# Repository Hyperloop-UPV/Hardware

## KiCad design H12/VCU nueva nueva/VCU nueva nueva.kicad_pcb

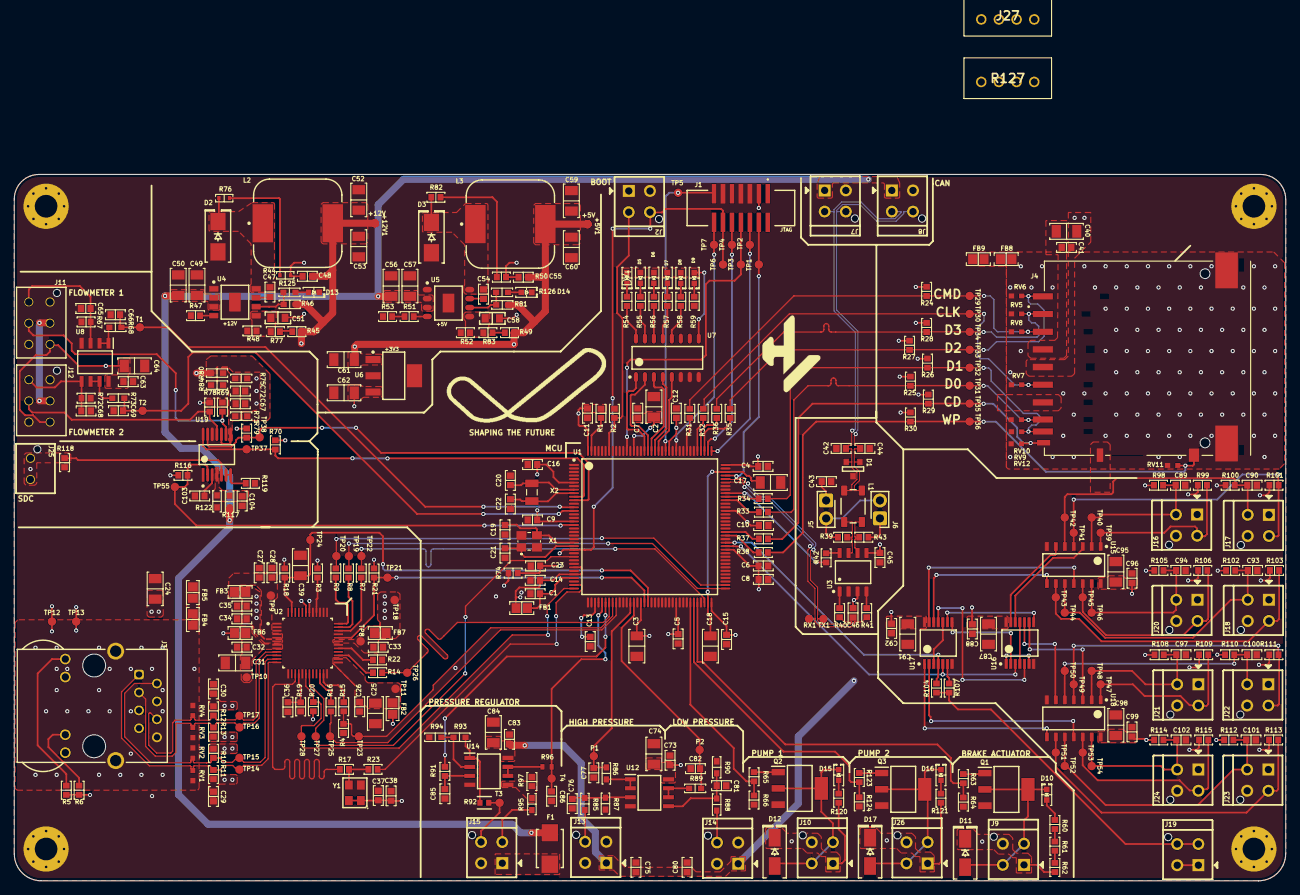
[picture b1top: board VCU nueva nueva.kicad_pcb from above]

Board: 6 copper layers, 180.0 x 100.0 mm, 388 parts (0 on the bottom side), 207 nets.

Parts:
+5V, +5V1, +12V, +12V1: Test point 1.2mm; Test point 1.2mm-Footprint-1
C1, C4, C5, C6, C7, C8, C9, C10, C11, C12, C13, C14, C15, C23, C26, C27, C28, C29, C30, C32, C33, C34, C37, C41, C45, C46, C47, C54, C63, C66, C67, C69, C72, C73, C75, C77, C80, C82, C83, C85, C86, C88, C89, C90, C92, C93, C94, C96, C97, C99, C100, C101, C102, C103, C104: 0.1 µF; CAP 0603_1608
C2, C24, C39, C40, C61, C62: 10 µF; CAP 1206_3216 - 0.8MM
C3: 4.7 µF; CAP 1206_3216 - 0.8MM
C16: 4700 pF; CAP 0603_1608
C17, C18: 2.2 µF; CAP 1206_3216 - 0.8MM
C19, C21: 12pF; CAP 0603_1608
C20, C22: 6.8 pF; CAP 0603_1608
C25, C31: 22 µF; CAP 1206_3216 - 0.8MM
C35, C38: 1 µF; CAP 0603_1608
C36: 100 pF; CAP 0603_1608
C42, C44: 47 pF; CAP 0603_1608
C43: 4700pF; CAP 0603_1608
C48: 1200 pF; CAP 0603_1608
C49, C50, C56, C57: 2.2µF; CAP 1206_3216 - 1.8MM
C51: 47 pF; MURATA GQM187 0603_1608
C52, C53, C59, C60: 22µF; CAP 1206_3216 - 1.8MM
C55: 2200pF; CAP 0603_1608
C58: 56 pF; MURATA GQM187 0603_1608
C64, C74, C84, C87, C91, C95, C98: 1 µF; CAP 1206_3216 - 0.8MM
C65, C68: 3300pF; CAP 0603_1608
C76, C81: 1500 pF; CAP 0603_1608
D1: PESD1CAN,215; PESD1CAN,215-Footprint-1
D2, D3: SK510BH-LTP; DO214AA SMB
D4, D9, D10, D13, D14, D15, D16: Green; LED 0603_1608 GREEN
D5: Red; LED 0603_1608 RED
D6: Blue; LED 0603_1608 BLUE
D7: Yellow; LED 0603_1608 YELLOW
D8: White; LED 0603_1608
D11, D12, D17: RS1B-13-F; DO214AC SMA
F1: 0308.500UR; New footprint 1
FB1, FB2, FB3, FB4, FB5, FB6, FB7, FB8, FB9: 120 Ohms @ 100 MHz; FER 0805_2012
J1: 3221-14-0300-00
J2, J7, J8, J9, J10, J13, J14, J15, J16, J17, J18, J19, J20, J21, J22, J23, J24, J26: 206832-0401; 206832-0401-Footprint-1
J3: 7499011222A
J4: 1939115-1; TE_1939115-1
J5, J6: 22-28-4020; 22-28-4020-Footprint-1
J11, J12: 206832-0602
J25: 216571-2002; 216571-2002-Footprint-1
J27: B4B-XH-A_LF__SN_; B4BXHALFSN
L1: DLW43SH510XK2L; FP-DLW43-0_2-t2_6-e0_7-MFG
L2: 7447709220; WE-PD_1210
L3: 744771112; WE-PD_1260
P1, P2: Test point 1.2mm; Test point 1.2mm-Footprint-1
Q1, Q2, Q3: BUK9875-100A/CUX; BUK9875-100A_CUX-Footprint-1
R1, R2, R3, R4, R18, R20, R21, R22, R24, R25, R26, R27, R28, R29, R30, R67, R69, R70, R72, R74, R78, R79, R116, R118, R119: 10 kOhms; RES 0603_1608
R5, R6, R63, R65, R123: 330 Ohms; RES 0603_1608
R7, R8, R9, R14, R15, R16, R17, R23, R31, R32, R33, R34, R35, R36, R37, R38: 33 Ohms; RES 0603_1608
R10, R11, R12, R13: 49.9 Ohms; RES 0603_1608
R19: 6.49 kOhms; RES 0603_1608
R39, R43: 62 Ohms; RES 0603_1608
R40, R41, R42: 100 Ohms; RES 0603_1608
R44: 330 kOhms; KOA RES RK73 RN73 0603_1608
R45: 220 kOhms; RES 0603_1608
R46: 10 kOhms; YAGEO RES 0603_1608
R47, R48, R52, R91: 100 kOhms; RES 0603_1608
R49: 56 kOhms; RES 0603_1608
R50, R97: 68 kOhms; RES 0603_1608
R51, R98, R99, R100, R101, R102, R103, R105, R106, R108, R109, R110, R111, R112, R113, R114, R115: 39 kOhms; RES 0603_1608
R53: 2.2 kOhms; RES 0603_1608
R54, R55, R56, R57, R58, R59, R60, R61, R62: 1 kOhms; RES 0603_1608
R64, R66, R124: 10kOhms; RES 0603_1608
R68, R73, R86, R89: 1 kOhms; YAGEO RES 0603_1608
R71, R80: 47kOhms; YAGEO RES 0603_1608
R75, R84, R94: 10kOhms; YAGEO RES 0603_1608
R76: 2.2 kOhms; KOA RES RK73 RN73 0603_1608
R77: 680 kOhms; RES 0603_1608
R81: 2.7 kOhms; YAGEO RES 0603_1608
R82: 180 kOhms; RES 0603_1608
R83: 270 kOhms; RES 0603_1608
R85, R88: 12kOhms; YAGEO RES 0603_1608
R87, R90: 33kOhms; YAGEO RES 0603_1608
R92: 0 Ohm; FP-CRG0603-IPC_C
R93: 5.1kOhms; YAGEO RES 0603_1608
R95: 39 kOhms; YAGEO RES 0603_1608
R96: 1kOhms; RESC1608X55X25LL10T15
R104, R107: 0 Ohms; RES 0603_1608
R117: 100 kOhms; YAGEO RES 0603_1608
R120, R121: 1.5 kOhms; RES 0603_1608
R122: 270 kOhms; YAGEO RES 0603_1608
R125, R126: 10 Ohms; YAGEO RES 0603_1608
R127: 4.7k; B4BXHALFSN
RV1, RV2, RV3, RV4, RV5, RV6, RV7, RV8, RV9, RV10, RV11, RV12: 82306050029; WE-VE ULC_0603
RX1: Test point 1.2mm; Test point 1.2mm-Footprint-1
SC1, SC2, SC3, SC4: M3 Screw; M3 Screw-Footprint-1
T1, T2, T3, T4: Test point 1.2mm; Test point 1.2mm-Footprint-1
TP1, TP2, TP3, TP4, TP5, TP6, TP7, TP8, TP9, TP10, TP11, TP12, TP13, TP14, TP15, TP16, TP17, TP18, TP19, TP20, TP21, TP22, TP23, TP24, TP25, TP26, TP27, TP28, TP29, TP30, TP31, TP32, TP33, TP34, TP35, TP36, TP37, TP38, TP39, TP40, TP41, TP42, TP43, TP44, TP45, TP46, TP47, TP48, TP49, TP50, TP51, TP52, TP53, TP54, TP55: Test point 1.2mm; Test point 1.2mm-Footprint-1
TX1: Test point 1.2mm; Test point 1.2mm-Footprint-1
U1: STM32H723ZG; TSQFP50P2200X2200X160-144N
U2: KSZ8041TLI; FP-TQFP7X7-48LD-PL-1-MFG
U3: TJA1051T/3,118; NXP-SOIC-8_N
U4, U5: LM5013-Q1; SOIC127P600X170_HS-9N
U6: LT1963AEST-3.3#TRPBF; SOT230P700X180-4N
U7: ULN2002A; SOIC16
U8, U12, U14: MCP6022-E/SN; SOIC-SN8_N
U15, U18: SN74HC32DR; D0014A_L
U16, U17: SN74ALVC08IPWRQ1; PW0014A_N
U19: LM339PWR; FP-PW0014A-IPC_A
X1: 25.000MHZ; ABM8G-25.000MHZ-18-D2Y-T-Footprint-1
X2: 32.768KHZ; ABS07-120-32.768KHZ-T-Footprint-1
Y1: 50 MHz; ABRACON ASE

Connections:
+3V3: C2.2, C3.2, C4.2, C5.2, C6.2, C7.2, C8.2, C9.2, C10.2, C11.2, C12.2, C13.2, C14.2, C15.2, C16.2, C24.2, C37.2, C38.2, C40.2, C41.2, C45.2, C62.2, C63.2, C64.1, C73.2, C74.1, C87.2, C88.2, C91.2, C92.2, C95.2, C96.2, C98.2, C99.2, D4.1, D5.1, D6.1, D7.1, D8.1, D9.1, FB1.2, FB2.2, FB6.2, J1.3 (VCC), J3.4 (CTD), J3.5 (CRD), J4.4, J11.4, J12.4, R1.2, R3.2, R5.2, R6.2, R18.2, R20.2, R21.2, R24.2, R25.2, R26.2, R27.2, R28.2, R29.2, R30.2, R69.2, R70.2, R74.1, R78.2, R79.2, R98.2, R99.2, R100.2, R101.2, R102.2, R103.2, R105.2, R106.2, R108.2, R109.2, R110.2, R111.2, R112.2, R113.2, R114.2, R115.2, R116.2, U1.6 (VBAT), U1.17 (VDD), U1.30 (VDD), U1.32 (VREF+), U1.39 (VDD), U1.52 (VDD), U1.62 (VDD), U1.72 (VDD), U1.84 (VDD), U1.95 (VDD33USB), U1.108 (VDD), U1.121 (VDD), U1.131 (VDD), U1.144 (VDD), U3.5 (VIO), U6.3 (OUT), U7.9, U8.8 (VDD), U12.8 (VDD), U15.14 (VCC), U16.14 (VCC), U17.14 (VCC), U18.14 (VCC), Y1.1 (TRI), Y1.4 (VDD)
+5V: +5V.1, +5V1.1 (*_1), C46.2, C55.2, C59.2, C60.2, C61.2, C75.2, C80.2, C83.2, C84.1, J13.1, J14.1, L3.2, R49.2, R81.2, U3.3 (VCC), U6.1 (IN), U14.8 (VDD)
+12V: +12V.1, +12V1.1 (*_1), C48.2, C52.2, C53.2, D12.2, D17.2, J10.1, J10.4, J11.5, J12.5, J26.1, J26.4, L2.2, R45.2, R46.2, R71.2, R80.2, R120.2, R121.2
+24: C103.2, U19.3 (VCC)
+24_SDC: D11.2, J9.1, J9.4, J25.1, J25.2, R62.2, R118.2, U19.5 (2IN+)
/Bomba_Refri/BOMBA_1: R65.1, R66.2
/Bomba_Refri/BOMBA_2: R123.1, R124.2
/Bomba_Refri/Bomba_TACH: J27.2, R127.2
/Braking_Sensor/GD_Reset_bypass: J19.3, J19.4, R104.2, R107.2
/Braking_Sensor/RESET: R104.1, U1.86 (PD15), U17.4 (2A)
/Braking_Sensor/SENSOR_1: J16.2, R99.1, TP39.1 (*_1), U15.1 (1A)
/Braking_Sensor/SENSOR_2: C89.2, J16.3, R98.1, TP40.1 (*_1), U15.2 (1B)
/Braking_Sensor/SENSOR_3: J17.2, R101.1, TP41.1 (*_1), U15.4 (2A)
/Braking_Sensor/SENSOR_4: C90.2, J17.3, R100.1, TP42.1 (*_1), U15.5 (2B)
/Braking_Sensor/SENSOR_5: J18.2, R103.1, TP43.1 (*_1), U15.9 (3A)
/Braking_Sensor/SENSOR_6: C93.2, J18.3, R102.1, TP44.1 (*_1), U15.10 (3B)
/Braking_Sensor/SENSOR_7: J20.2, R106.1, TP45.1 (*_1), U15.12 (4A)
/Braking_Sensor/SENSOR_8: C94.2, J20.3, R105.1, TP46.1 (*_1), U15.13 (4B)
/Braking_Sensor/SENSOR_9: J21.2, R109.1, TP47.1 (*_1), U18.1 (1A)
/Braking_Sensor/SENSOR_10: C97.2, J21.3, R108.1, TP48.1 (*_1), U18.2 (1B)
/Braking_Sensor/SENSOR_11: J22.2, R111.1, TP49.1 (*_1), U18.4 (2A)
/Braking_Sensor/SENSOR_12: C100.2, J22.3, R110.1, TP50.1 (*_1), U18.5 (2B)
/Braking_Sensor/SENSOR_13: J23.2, R113.1, TP51.1 (*_1), U18.9 (3A)
/Braking_Sensor/SENSOR_14: C101.2, J23.3, R112.1, TP52.1 (*_1), U18.10 (3B)
/Braking_Sensor/SENSOR_15: J24.2, R115.1, TP53.1 (*_1), U18.12 (4A)
/Braking_Sensor/SENSOR_16: C102.2, J24.3, R114.1, TP54.1 (*_1), U18.13 (4B)
/CAN/CAN1_N: R41.1, RX1.1 (*_1)
/CAN/CAN1_P: R40.1, TX1.1 (*_1)
/CAN/CANT_N: L1.4, R43.2, U3.6 (CANL)
/CAN/CANT_P: L1.1, R39.1, U3.7 (CANH)
/CAN/CAN_N: C44.1, D1.1, J7.4, J8.4, L1.3
/CAN/CAN_P: C42.2, D1.2, J7.3, J8.3, L1.2
/Caudalimetro/2.1V_Reference: C67.2, C72.2, R71.1, R75.2, R80.1, R84.2, U19.8 (3IN-), U19.10 (4IN-)
/Caudalimetro/FLOW_1: R70.1, TP37.1 (*_1), U1.10 (PF0), U19.14 (OUT3)
/Caudalimetro/FLOW_2: R79.1, TP38.1 (*_1), U1.11 (PF1), U19.13 (OUT4)
/Caudalimetro/FLOW_SENS_1: J11.2, R69.1, U19.9 (3IN+)
/Caudalimetro/FLOW_SENS_2: J12.2, R78.1, U19.11 (4IN+)
/Caudalimetro/NTC_TEMP_1: C66.2, R68.2, T1.1 (*_1), U1.13 (PF3)
/Caudalimetro/NTC_TEMP_2: C69.2, R73.2, T2.1 (*_1), U1.14 (PF4)
/Caudalimetro/TEMP_SENS_1: C65.1, J11.3, R67.1, U8.3 (VINA+)
/Caudalimetro/TEMP_SENS_2: C68.1, J12.3, R72.1, U8.5 (VINB+)
/Electrovalvula/ELECTROVALVULA: R63.1, R64.2, U1.68 (PE15)
/Ethernet_PHY/CONFIG0: R3.1, U2.40 (COL/CONFIG0)
/Ethernet_PHY/CRS: R14.2, TP26.1 (*_1), U1.43 (PA7)
/Ethernet_PHY/CRS_HF: R14.1, U2.27 (RXDV/CRSDV/CONFIG2)
/Ethernet_PHY/LAN_INTE: R21.1, TP21.1 (*_1), U1.53 (PF13), U2.32 (INTRP)
/Ethernet_PHY/LED0: J3.10, TP12.1 (*_1), U2.42 (LED0/NWAYEN)
/Ethernet_PHY/LED1: J3.12, TP13.1 (*_1), U2.43 (LED1/SPEED)
/Ethernet_PHY/MDC: TP27.1 (*_1), U1.27 (PC1), U2.19 (MDC)
/Ethernet_PHY/MDIO: R20.1, TP28.1 (*_1), U1.36 (PA2), U2.18 (MDIO)
/Ethernet_PHY/PHY_CLK_50M: R17.2, U2.15 (XI/REFCLK/CLOCK)
/Ethernet_PHY/PHY_RST: C39.2, R18.1, TP24.1 (*_1), U1.54 (PF14), U2.47 (~RST)
/Ethernet_PHY/REXT: C36.2, R19.2, U2.16 (REXT)
/Ethernet_PHY/RXD0: R4.2, R15.2, TP23.1 (*_1), U1.44 (PC4)
/Ethernet_PHY/RXD0_HF: R15.1, U2.23 (RXD0/RXD[0]/RX_DUPLEX)
/Ethernet_PHY/RXD1: R16.2, TP25.1 (*_1), U1.45 (PC5)
/Ethernet_PHY/RXD1_HF: R16.1, U2.22 (RXD1/RXD[1]/PHYAD2)
/Ethernet_PHY/RXER: R22.2, U2.29 (RXER/RX_ER/ISO)
/Ethernet_PHY/RX_N: J3.6 (RD-), R12.2, RV4.1, TP17.1 (*_1), U2.9 (RX-)
/Ethernet_PHY/RX_P: J3.3 (RD+), R13.2, RV3.1, TP16.1 (*_1), U2.10 (RX+)
/Ethernet_PHY/TXD0: R8.1, TP19.1 (*_1), U1.73 (PB12)
/Ethernet_PHY/TXD0_HF: R8.2, U2.35 (TXD0/TXD[0]/TX)
/Ethernet_PHY/TXD1: R9.1, TP20.1 (*_1), U1.74 (PB13)
/Ethernet_PHY/TXD1_HF: R9.2, U2.36 (TXD1/TXD[1]/SYNC)
/Ethernet_PHY/TXEN: R7.1, TP22.1 (*_1), U1.70 (PB11)
/Ethernet_PHY/TXEN_HF: R7.2, U2.34 (TXEN/TX_EN)
/Ethernet_PHY/TX_N: J3.2 (TD-), R10.2, RV2.1, TP15.1 (*_1), U2.11 (TX-)
/Ethernet_PHY/TX_P: J3.1 (TD+), R11.2, RV1.1, TP14.1 (*_1), U2.12 (TX+)
/Info_LEDs/LED_CAN: U1.125 (PG10), U7.4
/Info_LEDs/LED_CONNECTING: U1.126 (PG11), U7.3
/Info_LEDs/LED_FAULT: U1.127 (PG12), U7.2
/Info_LEDs/LED_OPERATIONAL: U1.128 (PG13), U7.1
/Info_LEDs/LED_SLEEP: U1.124 (PG9), U7.5
/MCU/BOOT: J2.3, R2.1, U1.138 (BOOT0)
/MCU/FAULT_BRAKE: U1.85 (PD14), U16.3 (1Y), U17.5 (2B)
/MCU/HIGH_PRESSURE: C77.2, P1.1 (*_1), R86.2, U1.49 (PF11)
/MCU/HSE_IN: C19.2, U1.23 (PH0-OSC_IN), X1.3 (XTAL2)
/MCU/HSE_OUT: C21.2, U1.24 (PH1-OSC_OUT), X1.1 (XTAL1)
/MCU/JTCK-SWCLK: J1.6 (JCLK/SWCLK), TP2.1 (*_1), U1.109 (PA14(SWCLK))
/MCU/JTDI: J1.10 (JTDI), TP4.1 (*_1), U1.110 (PA15(JTDI))
/MCU/JTDO-SWO: J1.8 (JTDO/SWO), TP3.1 (*_1), U1.133 (PB3(JTDO/TSWO))
/MCU/JTMS-SWDIO: J1.4 (JTMS/SWDIO), TP1.1 (*_1), U1.105 (PA13(SWDIO))
/MCU/LOW_PRESSURE: C82.2, P2.1 (*_1), R89.2, U1.50 (PF12)
/MCU/LSE_IN: C20.2, U1.8 (PC14-OSC32_IN), X2.2 (XTAL2)
/MCU/LSE_OUT: C22.2, U1.9 (PC15-OSC32_OUT), X2.1 (XTAL1)
/MCU/NRST: C23.2, J1.12 (NRST), J2.4, R74.2, TP6.1 (*_1), U1.25 (~nRST)
/MCU/REGULADOR_IN: R91.1, U1.42 (PA6)
/MCU/REGULADOR_OUT: C86.2, R96.2, T4.1 (*_1), U1.41 (PA5)
/MCU/SDC: R116.1, TP55.1 (*_1), U1.18 (PF6), U19.2 (2OUT)
/MCU/SDMMC_CD: R37.1, U1.89 (PG4)
/MCU/SDMMC_CLK: R32.1, U1.113 (PC12)
/MCU/SDMMC_CMD: R31.1, U1.116 (PD2)
/MCU/SDMMC_D0: R33.1, U1.98 (PC8)
/MCU/SDMMC_D1: R34.1, U1.99 (PC9)
/MCU/SDMMC_D2: R35.1, U1.111 (PC10)
/MCU/SDMMC_D3: R36.1, U1.112 (PC11)
/MCU/SDMMC_WP: R38.1, U1.88 (PG3)
/MCU/SLNT_MCU: R42.2, U1.100 (PA8)
/MCU/UART_RX: J1.13 (UART_RX), TP5.1 (*_1), U1.122 (PD6)
/MCU/UART_TX: J1.14 (UART_TX), TP7.1 (*_1), U1.119 (PD5)
/Power Supply/FB_5V: C58.1, R52.2, R83.1, U5.5 (FB)
/Power Supply/FB_12V: C51.1, R48.2, R77.1, U4.5 (FB)
/Power Supply/PGOOD_5V: R81.1, R126.2, U5.6 (PGOOD)
/Power Supply/PGOOD_12V: R46.1, R125.2, U4.6 (PGOOD)
/Regulador_Presion/3.18V: R95.1, R97.2, U14.5 (VINB+)
/Regulador_Presion/REG_IN: J15.4, R92.2, T3.1 (*_1)
/Regulador_Presion/REG_OUT: J15.3, R95.2
/Regulador_Presion/V_SUPPLY_1: F1.2, J15.1
/SD/SDMMC_CD_HF: J4.10 (CD), R29.1, R37.2, RV12.1, TP35.1 (*_1)
/SD/SDMMC_CLK_HF: J4.5, R32.2, RV7.1, TP30.1 (*_1)
/SD/SDMMC_CMD_HF: J4.2, R24.1, R31.2, RV8.1, TP29.1 (*_1)
/SD/SDMMC_D0_HF: J4.7, R25.1, R33.2, RV10.1, TP31.1 (*_1)
/SD/SDMMC_D1_HF: J4.8, R26.1, R34.2, RV9.1, TP32.1 (*_1)
/SD/SDMMC_D2_HF: J4.9, R27.1, R35.2, RV6.1, TP33.1 (*_1)
/SD/SDMMC_D3_HF: J4.1, R28.1, R36.2, RV5.1, TP34.1 (*_1)
/SD/SDMMC_WP_HF: J4.12 (WP), R30.1, R38.2, RV11.1, TP36.1 (*_1)
/SDC/18V_Reference: C104.2, R117.1, R122.2, U19.4 (2IN-)
/Transductores_Presion/PRESS_SENS_1: C76.2, R85.1, R87.2, U12.3 (VINA+)
/Transductores_Presion/PRESS_SENS_2: C81.2, R88.1, R90.2, U12.5 (VINB+)
ETH_Shield: FB4.1, J3.Shell (Shield), RV1.2, RV2.2, RV3.2, RV4.2
GND: C1.1, C2.1, C3.1, C4.1, C5.1, C6.1, C7.1, C8.1, C9.1, C10.1, C11.1, C12.1, C13.1, C14.1, C15.1, C16.1, C17.1, C18.1, C19.1, C20.1, C21.1, C22.1, C23.1, C24.1, C25.1, C26.1, C27.1, C28.1, C29.1, C30.1, C31.1, C32.1, C33.1, C34.1, C35.1, C36.1, C37.1, C38.1, C39.1, C40.1, C41.1, C42.1, C43.1, C44.2, C45.1, C46.1, C49.1, C50.1, C52.1, C53.1, C56.1, C57.1, C59.1, C60.1, C61.1, C62.1, C63.1, C64.2, C65.2, C66.1, C67.1, C68.2, C69.1, C72.1, C73.1, C74.2, C75.1, C76.1, C77.1, C80.1, C81.1, C82.1, C83.1, C84.2, C85.1, C86.1, C87.1, C88.1, C89.1, C90.1, C91.1, C92.1, C93.1, C94.1, C95.1, C96.1, C97.1, C98.1, C99.1, C100.1, C101.1, C102.1, C103.1, C104.1, D1.3, D2.1, D3.1, D13.2, D14.2, FB5.2, FB9.2, J1.5 (GND), J1.7 (GND), J1.11 (GND_Det), J2.1, J2.2, J3.8 (GND), J4.3, J4.6, J4.11 (COMM), J7.2, J8.2, J11.1, J11.6, J12.1, J12.6, J13.2, J13.3, J14.2, J14.3, J15.2, J16.1, J16.4, J17.1, J17.4, J18.1, J18.4, J19.1, J19.2, J20.1, J20.4, J21.1, J21.4, J22.1, J22.4, J23.1, J23.4, J24.1, J24.4, Q1.3 (S), Q2.3 (S), Q3.3 (S), R2.2, R4.1, R19.1, R22.1, R47.1, R48.1, R52.1, R53.1, R59.1, R64.1, R66.1, R67.2, R72.2, R75.1, R84.1, R87.1, R90.1, R94.1, R97.1, R118.1, R119.1, R122.1, R124.1, SC1.1 (1_1), SC2.1 (1_1), SC3.1 (1_1), SC4.1 (1_1), U1.1 (PE2), U1.2 (PE3), U1.3 (PE4), U1.4 (PE5), U1.5 (PE6), U1.7 (PC13), U1.12 (PF2), U1.15 (PF5), U1.16 (VSS), U1.19 (PF7), U1.20 (PF8), U1.21 (PF9), U1.22 (PF10), U1.26 (PC0), U1.28 (PC2_C), U1.29 (PC3_C), U1.31 (VSSA), U1.34 (PA0), U1.37 (PA3), U1.38 (VSS), U1.40 (PA4), U1.46 (PB0), U1.47 (PB1), U1.48 (PB2), U1.51 (VSS), U1.55 (PF15), U1.56 (PG0), U1.57 (PG1), U1.58 (PE7), U1.59 (PE8), U1.60 (PE9), U1.61 (VSS), U1.63 (PE10), U1.64 (PE11), U1.65 (PE12), U1.69 (PB10), U1.75 (PB14), U1.76 (PB15), U1.77 (PD8), U1.78 (PD9), U1.79 (PD10), U1.80 (PD11), U1.81 (PD12), U1.82 (PD13), U1.83 (VSS), U1.87 (PG2), U1.90 (PG5), U1.91 (PG6), U1.92 (PG7), U1.93 (PG8), U1.94 (VSS), U1.96 (PC6), U1.97 (PC7), U1.101 (PA9), U1.102 (PA10), U1.107 (VSS), U1.114 (PD0), U1.115 (PD1), U1.117 (PD3), U1.118 (PD4), U1.120 (VSS), U1.123 (PD7), U1.129 (PG14), U1.130 (VSS), U1.132 (PG15), U1.134 (PB4(~nJTRST)), U1.135 (PB5), U1.136 (PB6), U1.137 (PB7), U1.139 (PB8), U1.140 (PB9), U1.141 (PE0), U1.142 (PE1), U2.1 (GND), U2.2 (GND), U2.3 (GND), U2.13 (GND), U2.17 (GND), U2.24 (GND), U2.30 (GND), U2.33 (TXC), U2.37 (GND), U2.38 (TXD2), U2.39 (TXD3), U2.41 (CRS/CONFIG1), U3.2 (GND), U4.1 (GND), U4.9 (PGND), U5.1 (GND), U5.9 (PGND), U6.2 (GND), U6.4 (TAB), U7.6, U7.7, U7.8, U8.4 (VSS), U12.4 (VSS), U14.4 (VSS), U15.7 (GND), U16.7 (GND), U17.7 (GND), U18.7 (GND), U19.12 (GND), X1.2 (GND), X1.4 (GND), Y1.2 (GND)
unnamed: C29.2, R10.1, R11.1
unnamed: C30.2, R12.1, R13.1
unnamed: C43.2, J5.1
unnamed: C48.1, C51.2, R44.2
unnamed: C55.1, C58.2, R50.2
unnamed: D4.2, R54.2
unnamed: D5.2, R55.2
unnamed: D6.2, R56.2
unnamed: D7.2, R57.2
unnamed: D8.2, R58.2
unnamed: D9.2, R59.2
unnamed: D10.1, R60.1
unnamed: D10.2, D11.1, J9.2, J9.3, Q1.2 (D), Q1.4 (D)
unnamed: D12.1, D15.2, J10.2, J10.3, Q2.2 (D), Q2.4 (D)
unnamed: D13.1, R125.1
unnamed: D14.1, R126.1
unnamed: D15.1, R120.1
unnamed: D16.1, R121.1
unnamed: D16.2, D17.1, J26.2, J26.3, Q3.2 (D), Q3.4 (D)
unnamed: FB4.2, FB5.1
unnamed: FB8.2, FB9.1
unnamed: J3.9, R5.1
unnamed: J3.11, R6.1
unnamed: J5.2, J6.2, R39.2
unnamed: J6.1, R43.1
unnamed: J13.4, R85.2
unnamed: J14.4, R88.2
unnamed: Q1.1 (G), R63.2
unnamed: Q2.1 (G), R65.2
unnamed: Q3.1 (G), R123.2
unnamed: R44.1, R76.2
unnamed: R45.1, R77.2
unnamed: R49.1, R83.2
unnamed: R50.1, R82.2
unnamed: R51.2, R53.2
unnamed: R54.1, U7.16
unnamed: R55.1, U7.15
unnamed: R56.1, U7.14
unnamed: R57.1, U7.13
unnamed: R58.1, U7.12
unnamed: R60.2, R61.1
unnamed: R61.2, R62.1
unnamed: R1.1, U1.143 (PDR_ON)
unnamed: R41.2, U3.4 (RXD)
unnamed: R42.1, U3.8 (S)
unnamed: R40.2, U3.1 (TXD)
unnamed: C47.1, U4.7 (BST)
unnamed: R47.2, U4.4 (RON)
unnamed: C47.2, D2.2, L2.1, R76.1, U4.8 (SW)
unnamed: C54.1, U5.7 (BST)
unnamed: R51.1, U5.4 (RON)
unnamed: C54.2, D3.2, L3.1, R82.1, U5.8 (SW)
unnamed: R68.1, U8.1 (VOUTA), U8.2 (VINA-)
unnamed: R73.1, U8.6 (VINB-), U8.7 (VOUTB)
unnamed: R86.1, U12.1 (VOUTA), U12.2 (VINA-)
unnamed: R89.1, U12.6 (VINB-), U12.7 (VOUTB)
unnamed: C85.2, R91.2, U14.3 (VINA+)
unnamed: R93.2, R94.2, U14.2 (VINA-)
unnamed: R92.1, R93.1, U14.1 (VOUTA)
unnamed: R96.1, U14.6 (VINB-), U14.7 (VOUTB)
unnamed: U15.3 (1Y), U16.12 (4A)
unnamed: U15.6 (2Y), U16.13 (4B)
unnamed: U15.8 (3Y), U17.12 (4A)
unnamed: U15.11 (4Y), U17.13 (4B)
unnamed: U16.1 (1A), U16.6 (2Y)
unnamed: U16.2 (1B), U17.8 (3Y)
unnamed: U16.4 (2A), U16.11 (4Y)
unnamed: U16.5 (2B), U17.11 (4Y)
unnamed: U16.9 (3A), U18.3 (1Y)
unnamed: U16.10 (3B), U18.6 (2Y)
unnamed: U16.8 (3Y), U17.9 (3A)
unnamed: U17.1 (1A), U18.8 (3Y)
unnamed: U17.2 (1B), U18.11 (4Y)
unnamed: U17.3 (1Y), U17.10 (3B)
unnamed: R107.1, U17.6 (2Y)
unnamed: R119.2, U19.6 (1IN-), U19.7 (1IN+)
unnamed: R17.1, R23.1, Y1.3 (OUT)
SD_Shield: FB8.1, J4.SH1 (SHIELD), J4.SH2 (SHIELD), RV5.2, RV6.2, RV7.2, RV8.2, RV9.2, RV10.2, RV11.2, RV12.2
V1.8_OUT: C34.2, C35.2, FB3.2, FB7.2, TP18.1 (*_1), U2.6 (V1.8_OUT)
VBAT: C49.2, C50.2, C56.2, C57.2, F1.1, J7.1, J8.1, R117.2, U4.2 (VIN), U4.3 (EN), U5.2 (VIN), U5.3 (EN)
VCAP_M: C17.2, C18.2, U1.71 (VCAP), U1.106 (VCAP)
VDDA_1.8: C27.2, C28.2, FB3.1, TP9.1 (*_1), U2.4 (VDDA_1.8), U2.5 (VDDA_1.8)
VDDA_3.3: C31.2, C32.2, FB6.1, TP10.1 (*_1), U2.7 (VDDA_3.3), U2.8 (VDDA_3.3)
VDDA_M: C1.2, FB1.1, U1.33 (VDDA)
VDDIO_3.3: C25.2, C26.2, FB2.1, TP11.1 (*_1), U2.25 (VDDIO_3.3), U2.26 (VDDIO_3.3)
VDD_1.8: C33.2, FB7.1, TP8.1 (*_1), U2.31 (VDD_1.8)

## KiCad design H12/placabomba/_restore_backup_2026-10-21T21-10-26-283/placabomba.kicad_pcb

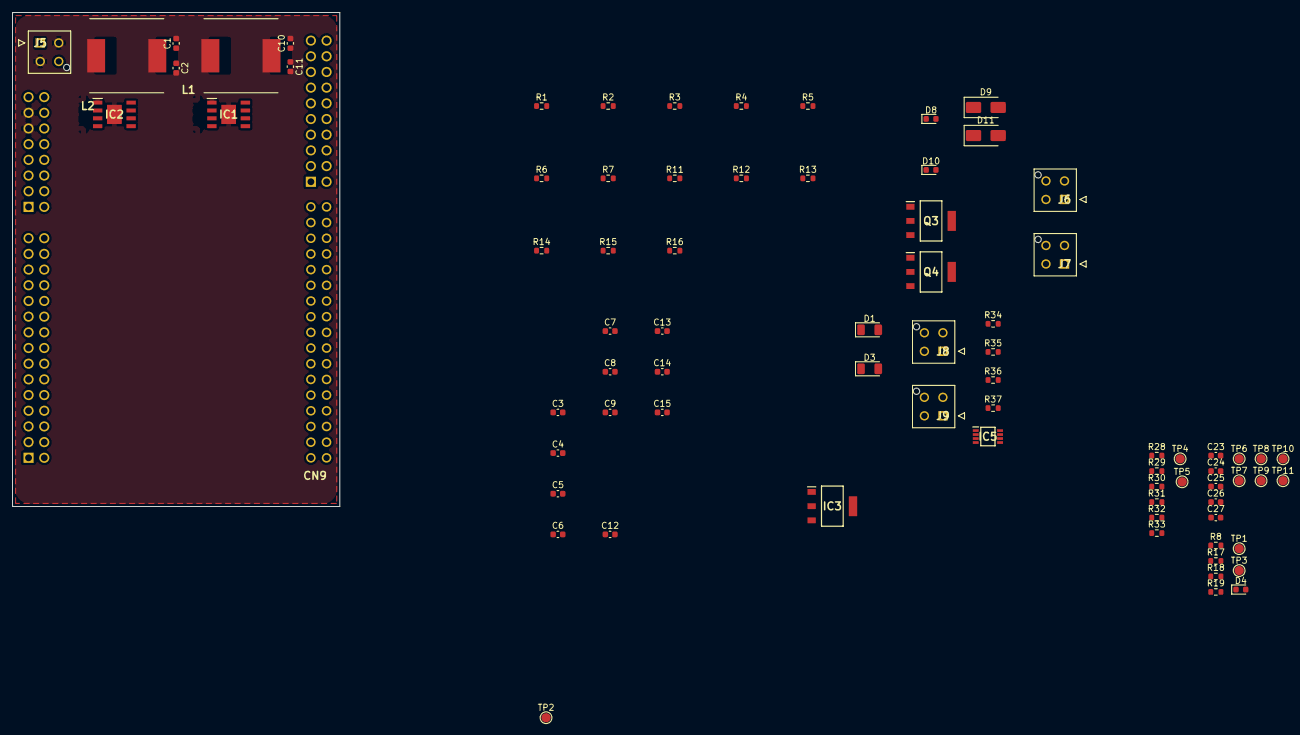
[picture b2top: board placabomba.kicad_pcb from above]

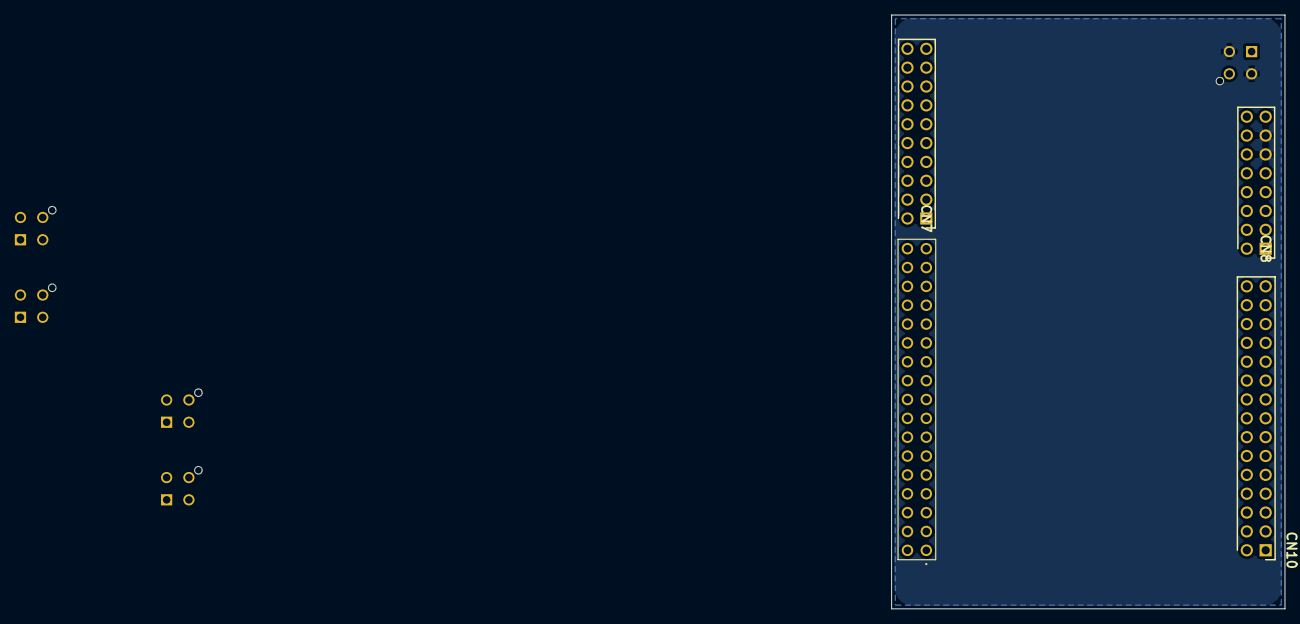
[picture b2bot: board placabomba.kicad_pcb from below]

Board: 2 copper layers, 53.0 x 80.0 mm, 82 parts (4 on the bottom side), 39 nets, no tracks yet.

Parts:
C1, C2, C10, C11: 2.2uF; C_0603_1608Metric
C3, C12, C23, C26, C27: 0.1uF; C_0603_1608Metric
C4: 56pF; C_0603_1608Metric
C5: 2200pF; C_0603_1608Metric
C6, C7, C15: 22uF; C_0603_1608Metric
C8, C9: 10uF; C_0603_1608Metric
C13: 47pF; C_0603_1608Metric
C14: 1200pF; C_0603_1608Metric
C24, C25: 100uF; C_0603_1608Metric
CN7: TSW-110-23-G-D; HDRV20W64P254_2X10_2540X495X838P
CN8: TSW-108-23-G-D; HDRV16W64P254_2X8_2032X495X838P
CN9: TSW-115-23-G-D; TSW-117-XX-YY-D
CN10: TSW-117-07-G-D; HDRV30W64P254_2X15_3810X508X838P
D1, D3: SK510BH-LTP; D_1206_3216Metric
D4, D8, D10: LED; LED_0603_1608Metric
D9, D11: SS36; D_SMA
IC1, IC2: LM5013QDDARQ1; SOIC127P600X170-9N
IC3: LT1963AEST-3.3#TRPBF; SOT230P700X180-4N
IC5: 74AHCT2G125DP-Q10H; SOP65P400X110-8N
J5, J6, J7, J8, J9: 2068320401; 20683204YY
L1, L2: 744771112
Q3, Q4: BUK9875-100A_CUX; SOT230P700X180-4N
R1: 39k; R_0603_1608Metric
R2, R12: 2.2k; R_0603_1608Metric
R3: 180k; R_0603_1608Metric
R4: 68k; R_0603_1608Metric
R5: 270k; R_0603_1608Metric
R6: 56k; R_0603_1608Metric
R7, R11, R16: 100k; R_0603_1608Metric
R8: 2.7k; R_0603_1608Metric
R13: 330k; R_0603_1608Metric
R14: 220k; R_0603_1608Metric
R15: 680k; R_0603_1608Metric
R17, R19: 10; R_0603_1608Metric
R18: 10k; R_0603_1608Metric
R28, R31: 10K; R_0603_1608Metric
R29, R32, R35, R36: 330; R_0603_1608Metric
R30, R33: 1.5K; R_0603_1608Metric
R34, R37: 4.7k; R_0603_1608Metric
TP1: +5V; TestPoint_Pad_D1.5mm
TP2: +3V3; TestPoint_Pad_D1.5mm
TP3: +12V; TestPoint_Pad_D1.5mm
TP4: POWER1; TestPoint_Pad_D1.5mm
TP5: POWER2; TestPoint_Pad_D1.5mm
TP6: TACHO1; TestPoint_Pad_D1.5mm
TP7: CONTROL1_IN; TestPoint_Pad_D1.5mm
TP8: CONTROL2_IN; TestPoint_Pad_D1.5mm
TP9: TACHO2; TestPoint_Pad_D1.5mm
TP10: LED1; TestPoint_Pad_D1.5mm
TP11: LED2; TestPoint_Pad_D1.5mm

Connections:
+3V3: C9.1, IC3.3 (OUT), R34.1, R37.1, TP2.1 (1_1)
+5V: C5.1, C6.1, C7.1, C8.1, C23.1, C24.1, C25.1, C26.1, C27.1, IC3.1 (IN), IC5.8 (VCC), J8.4, J9.4, L1.2, R6.2, TP1.1 (1_1)
+12V: C14.1, C15.1, D9.1 (K), D11.1 (K), L2.2, R14.2, R30.1, R33.1, TP3.1 (1_1)
+24V: C1.1, C2.1, C10.1, C11.1, IC1.2 (VIN), IC1.3 (EN/UVLO), IC2.2 (VIN), IC2.3 (EN/UVLO), J5.1, J5.4
/Buckconverter/FB_5V: C4.1, IC1.5 (FB), R5.1, R7.2
/Buckconverter/FB_12V: C13.1, IC2.5 (FB), R15.1, R16.2
/Buckconverter/PGOOD_5V: IC1.6 (PGOOD), R8.2, R17.1
/Buckconverter/PGOOD_12V: IC2.6 (PGOOD), R18.2, R19.1
/bombacontrol/CONTROL1: CN7.16, J6.4, TP7.1 (1_1)
/bombacontrol/CONTROL2: CN7.14, J7.4, TP8.1 (1_1)
/bombacontrol/TACHO1: CN7.18, J6.3, R34.2, TP6.1 (1_1)
/bombacontrol/TACHO2: J7.3, R37.2, TP9.1 (1_1)
/bombapower/POWER1: D8.1 (K), D9.2 (A), J6.1, Q3.2 (D_1), Q3.4 (D_2), TP4.1 (1_1)
/bombapower/POWER1_CONTROL: CN10.4, R28.1, R29.1
/bombapower/POWER2: D10.1 (K), D11.2 (A), J7.1, Q4.2 (D_1), Q4.4 (D_2), TP5.1 (1_1)
/bombapower/POWER2_CONTROL: CN10.6, R31.1, R32.1
GND: C1.2, C2.2, C6.2, C7.2, C8.2, C9.2, C10.2, C11.2, C15.2, C23.2, C24.2, C25.2, C26.2, C27.2, CN8.11, CN8.13, D1.2 (A), D3.2 (A), D4.1 (K), IC1.1 (GND), IC1.9 (EP), IC2.1 (GND), IC2.9 (EP), IC3.2 (GND_1), IC3.4 (GND_2), IC5.1 (~1OE), IC5.4 (GND), IC5.7 (~2OE), J5.2, J5.3, J6.2, J7.2, J8.3, J9.3, Q3.3 (S), Q4.3 (S), R2.2, R7.1, R11.2, R16.1, R19.2, R28.2, R31.2
unnamed: C4.2, C5.2, R4.2
unnamed: C13.2, C14.2, R13.2
unnamed: C3.2, D1.1 (K), IC1.8 (SW), L1.1, R3.1, R8.1
unnamed: C12.2, D3.1 (K), IC2.8 (SW), L2.1, R12.1, R18.1
unnamed: D4.2 (A), R17.2
unnamed: D8.2 (A), R30.2
unnamed: D10.2 (A), R33.2
unnamed: C3.1, IC1.7 (BST)
unnamed: IC1.4 (RON), R1.1
unnamed: C12.1, IC2.7 (BST)
unnamed: IC2.4 (RON), R11.1
unnamed: IC5.6 (1Y), R35.1
unnamed: IC5.3 (2Y), R36.1
unnamed: J8.2, R35.2, TP10.1 (1_1)
unnamed: J9.2, R36.2, TP11.1 (1_1)
unnamed: Q3.1 (G), R29.2
unnamed: Q4.1 (G), R32.2
unnamed: R1.2, R2.1
unnamed: R3.2, R4.1
unnamed: R5.2, R6.1
unnamed: R12.2, R13.1
unnamed: R14.1, R15.2

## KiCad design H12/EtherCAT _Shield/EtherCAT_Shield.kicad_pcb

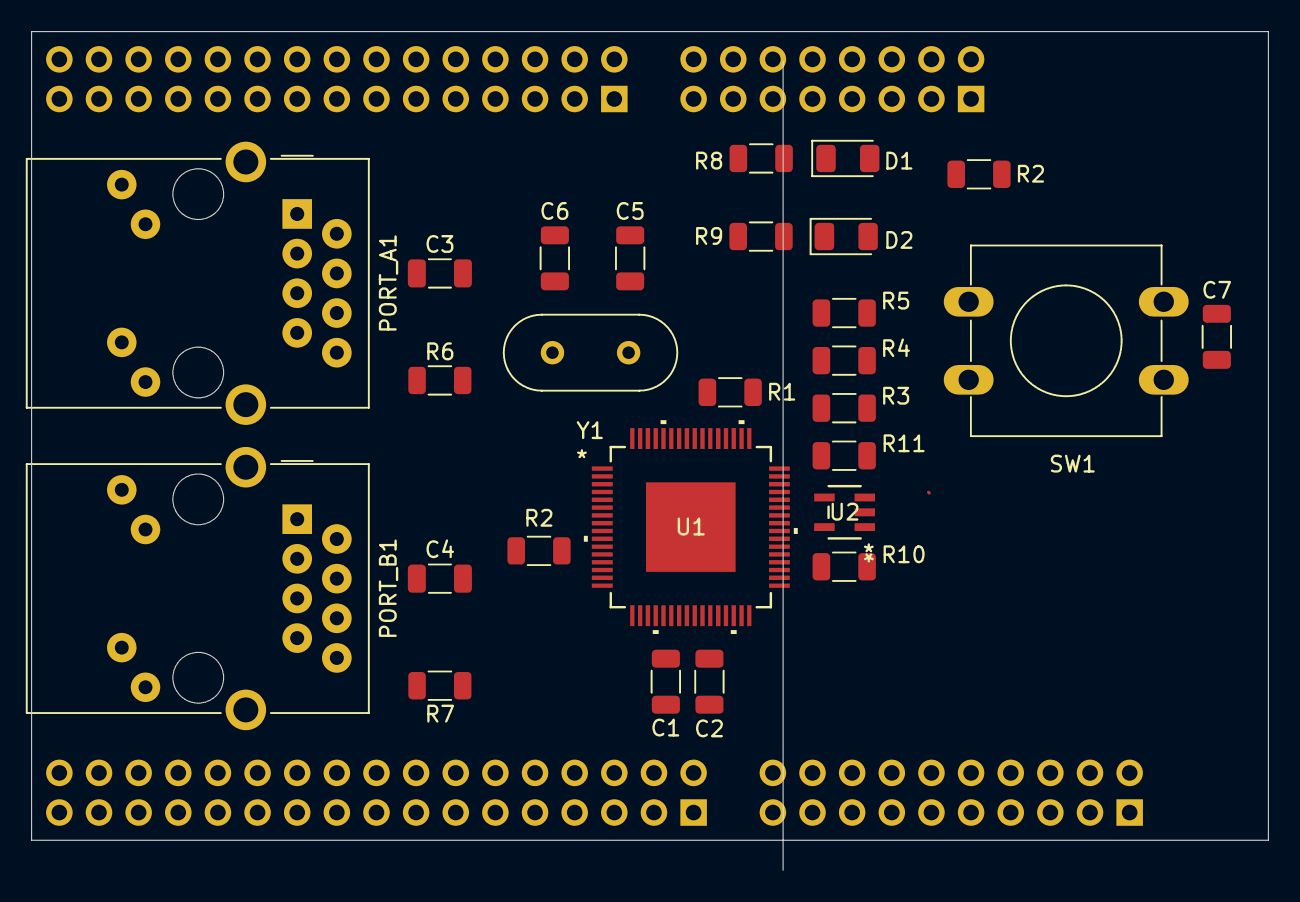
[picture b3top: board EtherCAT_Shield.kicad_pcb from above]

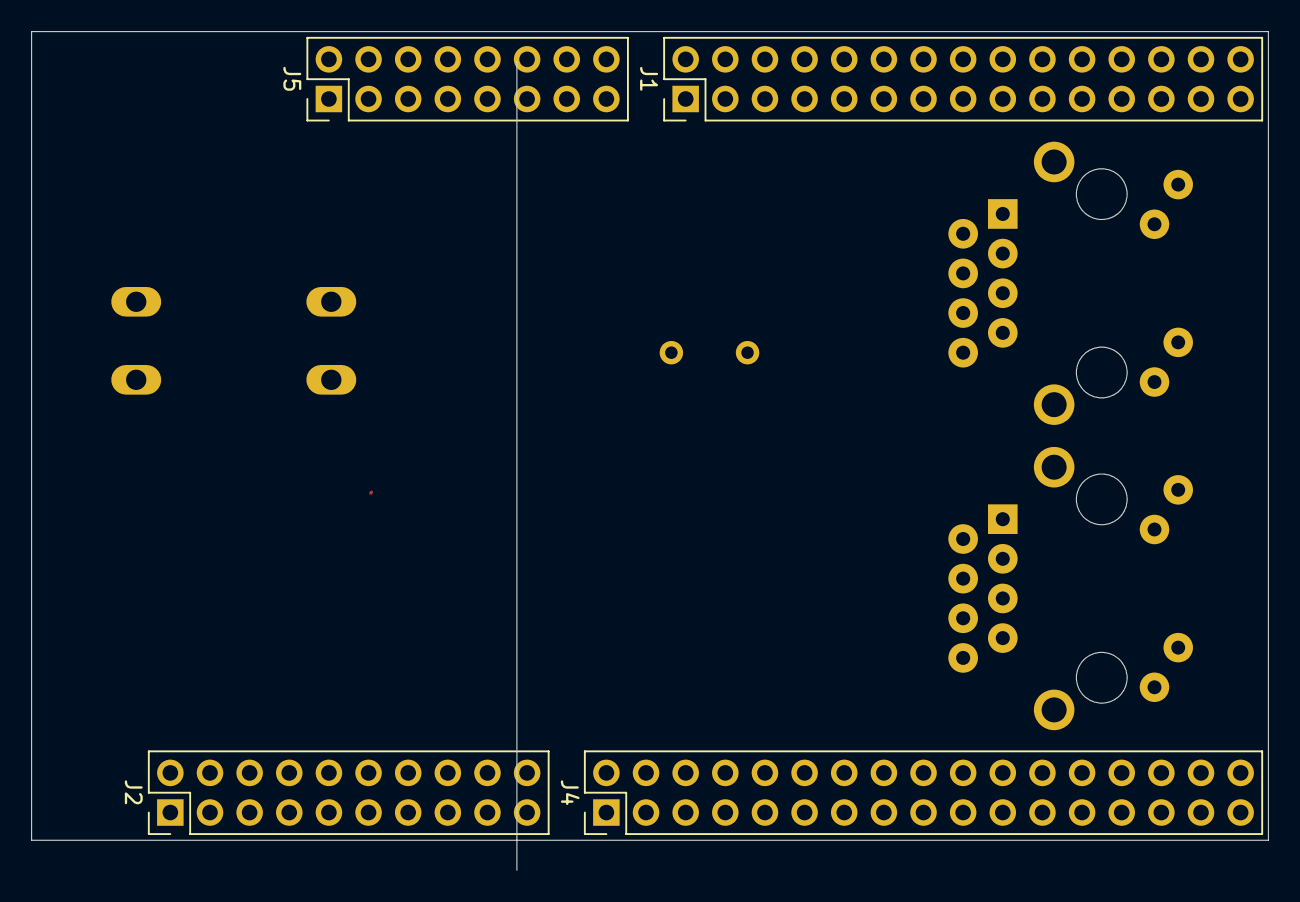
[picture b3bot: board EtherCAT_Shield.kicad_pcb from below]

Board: 2 copper layers, 79.2 x 53.7 mm, 31 parts (4 on the bottom side), 29 nets.

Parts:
C1: 1uF; C_1206_3216Metric
C2: 470pF; C_1206_3216Metric
C3, C4: 22nF; C_1206_3216Metric
C5, C6: 30pF; C_1206_3216Metric
C7: 100nF; C_1206_3216Metric
D1: LED_POWER; LED_1206_3216Metric
D2: LED_RUN; LED_1206_3216Metric
J1: Conn_02x15_Odd_Even; PinHeader_2x15_P2.54mm_Vertical
J2: Conn_02x10_Odd_Even; PinHeader_2x10_P2.54mm_Vertical
J4: Conn_02x17_Odd_Even; PinHeader_2x17_P2.54mm_Vertical
J5: Conn_02x08_Odd_Even; PinHeader_2x08_P2.54mm_Vertical
PORT_A1: RJ45_Amphenol_RJMG1BD3B8K1ANR
PORT_B1: RJ45_Amphenol_RJMG1BD3B8K1ANR
R1: 12.1K 1%; R_1206_3216Metric
R2, R2#2: 1K; R_1206_3216Metric
R3, R4, R5, R10, R11: 4.7K; R_1206_3216Metric
R6, R7, R8, R9: 330; R_1206_3216Metric
SW1: RESET; SW_PUSH-12mm
U1: LAN9252I/PT; TQFP-EP64_PT_MCH
U2: 24AA64T-E/OT; SOT-23-5_MC_MCH
Y1: Crystal; Crystal_HC49-U_Vertical

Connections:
+3.3V: C3.1, C4.1, D1.2 (A), J5.7, PORT_A1.R4 (TCT), PORT_A1.R5 (RCT), PORT_B1.R4 (TCT), PORT_B1.R5 (RCT), R2.1, R2#2.1, R3.1, R10.2, R11.2, U1.5 (VDD33), U1.7 (REG_EN), U1.14 (VDDIO), U1.20 (VDDIO), U1.32 (VDDIO), U1.37 (VDDIO), U1.47 (VDDIO), U1.51 (VDD33TXRX1), U1.58 (VDD33BIAS), U1.64 (VDD33TXRX2), U2.4 (VCC)
/ACTLED0: R4.1, R6.2, U1.48 (LINKACTLED0/TDO/CHIP_MODE0)
/ACTLED1: R5.1, R7.1, U1.46 (LINKACTLED1/TDI/CHIP_MODE1)
/EEPROM_SCL: R11.1, U1.43 (EESCL/TCK), U2.1 (SCL)
/EEPROM_SDA: R10.1, U1.42 (EESDA/TMS), U2.3 (SDA)
/OSCI: C6.2, U1.1 (OSCI), Y1.1
/OSCO: C5.2, U1.2 (OSCO), Y1.2
/RST: C7.2, R2#2.2, SW1.2 (B), U1.11 (RST#)
/RUNLED: D2.2 (A), R3.2, U1.45 (RUNLED/E2PSIZE)
/SQI_CS: J4.13, U1.50 (D5/AD5/OUTVALID/SCS#)
/SQI_D0: J4.23, U1.17 (D0/AD0/WD_STATE/SI/SIO0)
/SQI_D1: J4.21, U1.13 (D1/AD1/EOF/SO/SIO1)
/SQI_D2: J4.25, U1.12 (D2/AD2/SOF/SIO2)
/SQI_D3: J4.19, U1.35 (D3/AD3/WD_TRIG/SIO3)
GND: C1.2, C2.2, C3.2, C4.2, C5.1, C6.1, C7.1, J1.12, J1.23, J2.8 (Pin_8_8), J4.5, J4.17, J4.22, J4.27, J5.11, J5.13, PORT_A1.L2, PORT_A1.L3, PORT_A1.R8, PORT_A1.SH, PORT_B1.L2, PORT_B1.L3, PORT_B1.R8, PORT_B1.SH, R1.1, R4.2, R5.2, R8.1, R9.1, SW1.1 (A), U1.4 (OSCVSS), U1.9 (FXSDA/FXLOSA/FXSDENA), U1.10 (FXSDB/FXLOSB/FXSDENB), U1.41 (TESTMODE), U1.EPAD (VSS), U2.2 (VSS), U2.5 (WP)
unnamed: D1.1 (K), R8.2
unnamed: D2.1 (K), R9.2
unnamed: PORT_A1.L1, PORT_A1.L4, R6.1
unnamed: PORT_A1.R3 (RD+), U1.55 (RXPA)
unnamed: PORT_A1.R6 (RD-), U1.54 (RXNA)
unnamed: PORT_A1.R1 (TD+), U1.53 (TXPA)
unnamed: PORT_A1.R2 (TD-), U1.52 (TXNA)
unnamed: PORT_B1.L1, PORT_B1.L4, R7.2
unnamed: PORT_B1.R3 (RD+), U1.60 (RXPB)
unnamed: PORT_B1.R6 (RD-), U1.61 (RXNB)
unnamed: PORT_B1.R1 (TD+), U1.62 (TXPB)
unnamed: PORT_B1.R2 (TD-), U1.63 (TXNB)
unnamed: R1.2, U1.57 (RBIAS)
unnamed: C1.1, C2.1, U1.6 (VDDCR), U1.24 (VDDCR), U1.38 (VDDCR), U1.56 (VDD12TX1), U1.59 (VDD12TX2)
